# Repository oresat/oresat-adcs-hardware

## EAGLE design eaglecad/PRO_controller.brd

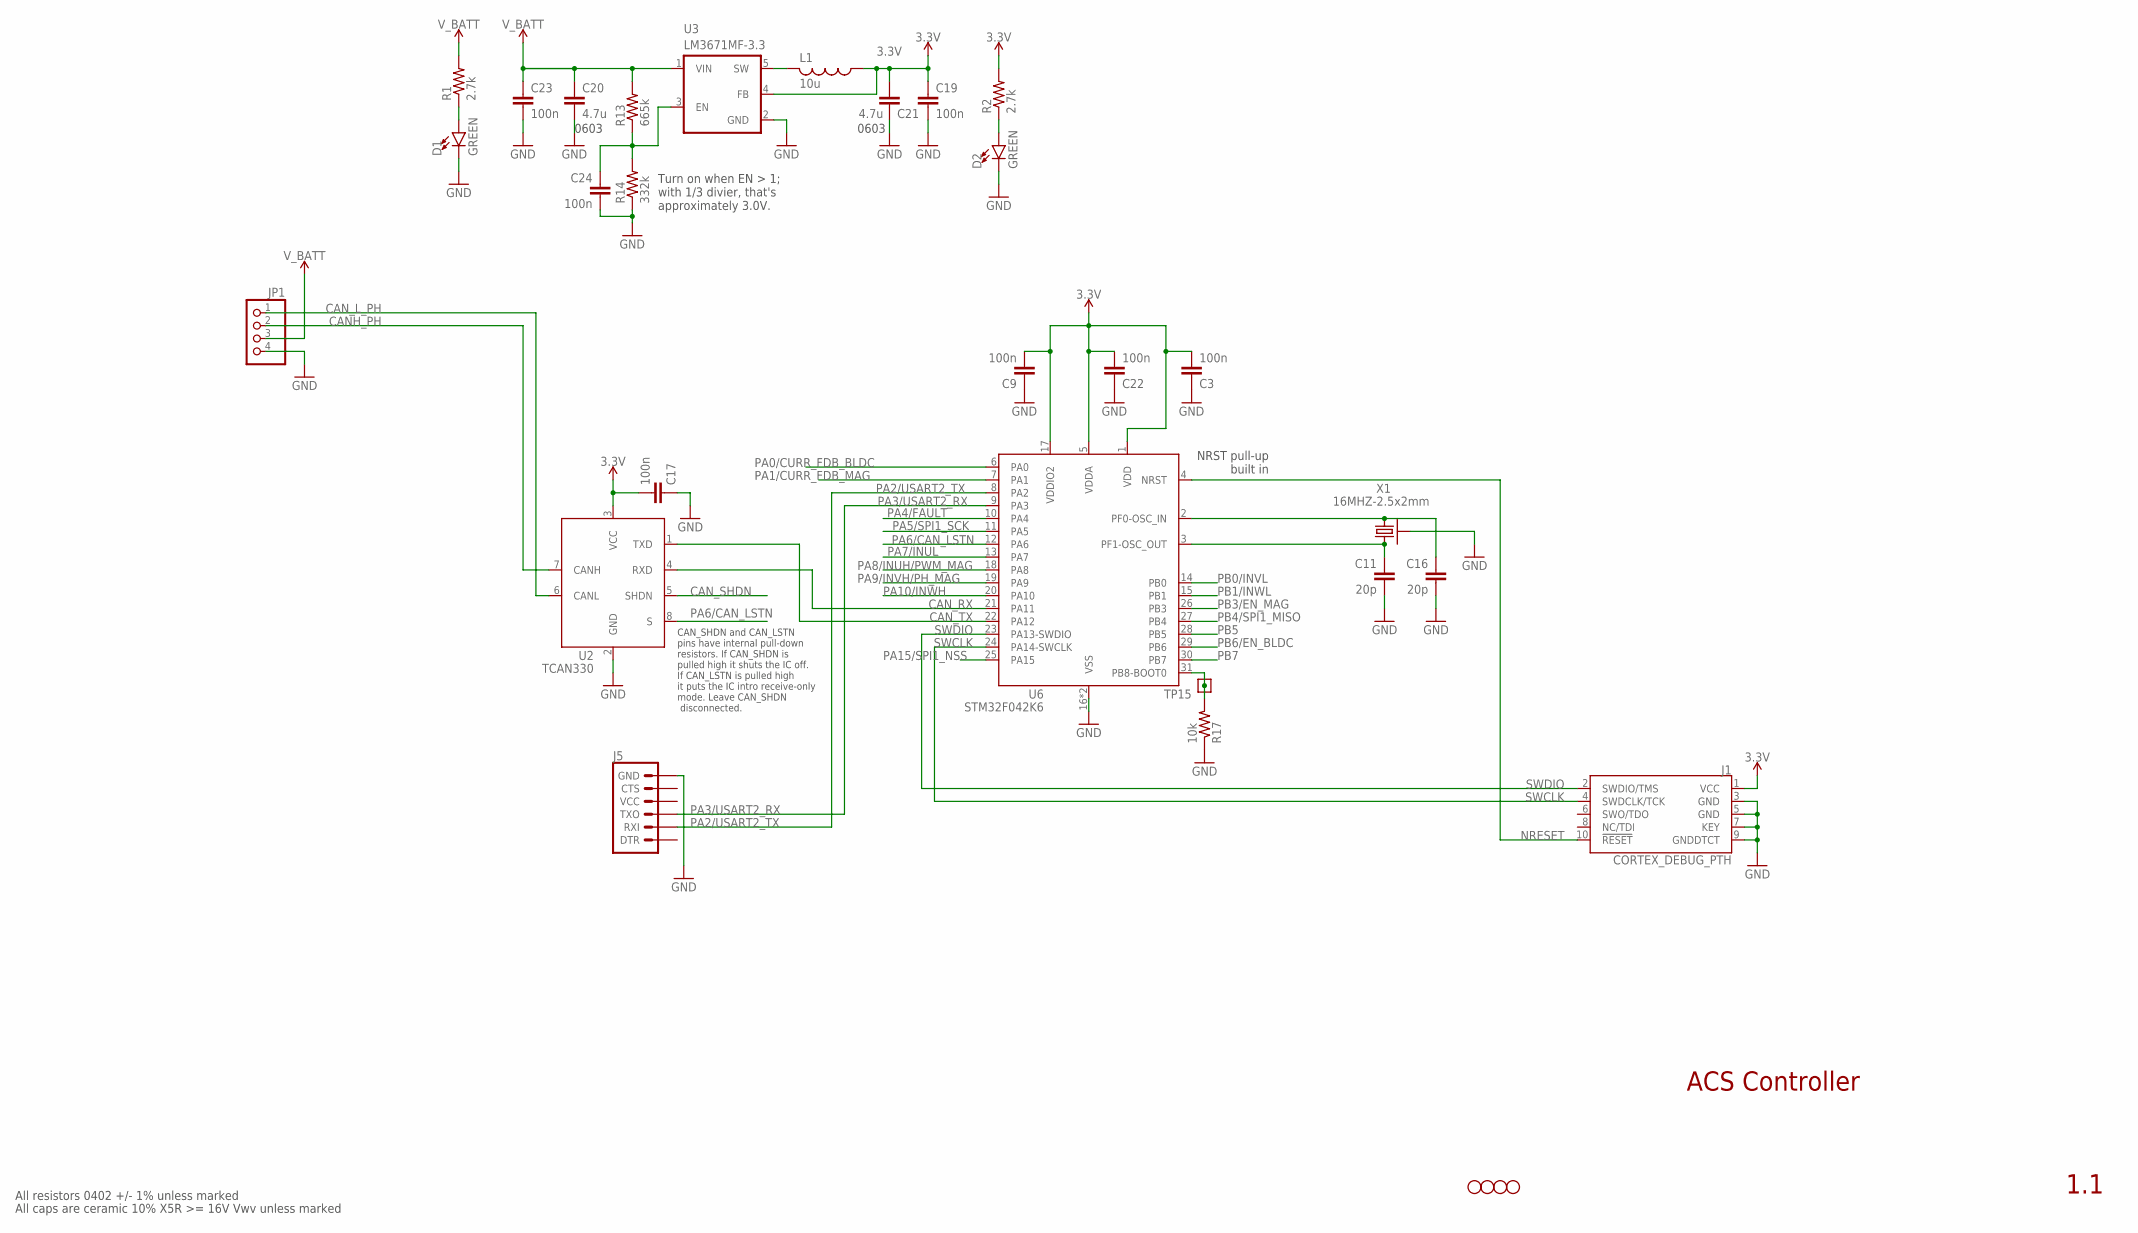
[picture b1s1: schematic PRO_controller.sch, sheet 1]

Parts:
C3, C9, C17, C19, C22, C23, C24: 100n; .0402-B-NOSILK; MPN CL05B104KO5NNNC
C11, C16: 20p; .0402-B-NOSILK; MPN CL05C200JB51PNC
C20, C21: 4.7u; C0603; MPN CL05B104KO5NNNC
D1, D2: GREEN; LED-0603
H1, H2, H3, H4: STAND-OFFTIGHT; STAND-OFF-TIGHT
J1: CORTEX_DEBUG_PTH; 2X5-PTH-1.27MM
J5: 6_PIN_SERIAL_TARGETSILK; 6_PIN_SERIAL_TARGET_SIDE_W_SILK
JP1: PINHD-1X4; 1X04
L1: 10u; L2012C; MPN CB2012T100KR
R1, R2: 2.7k; .0402-B-NOSILK; MPN RC1005F6653CS
R13: 665k; .0402-B-NOSILK; MPN RC1005F6653CS
R14: 332k; .0402-B-NOSILK; MPN RC1005F3323CS
R17: 10k; .0402-B-NOSILK; MPN RC1005F6653CS
TP15: TEST-POINT; 2MM-TEST-POINT
U2: TCAN330; SOT23-8_TI-DCN; MPN TCAN330GDCNT
U3: LM3671MF-3.3; SOT23-5; MPN LM3671MF-3.3/NOPB
U6: STM32F042K6; QFP32-7X7; MPN STM32F042K6T7
X1: 16MHZ-2.5x2mm; CRYSTAL_2.5X2; MPN ECS-160-10-36Q-ES-TR

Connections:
3.3V: C3.2, C9.2, C17.2, C19.1, C21.1, C22.2, J1.1 (VCC), L1.1, R2.2, U2.3 (VCC), U3.4 (FB), U6.1 (VDD), U6.5 (VDDA), U6.17 (VDDIO2); also elsewhere on the board
BOOT: R17.2, TP15.1, U6.31 (PB8-BOOT0)
CANH_PH: JP1.2, U2.7 (CANH)
CAN_L_PH: JP1.1, U2.6 (CANL)
CAN_RX: U2.4 (RXD), U6.21 (PA11)
CAN_SHDN: U2.5 (SHDN)
CAN_TX: U2.1 (TXD), U6.22 (PA12)
CRYSTALIN: C16.1, U6.2 (PF0-OSC_IN), X1.1
CRYSTALOUT: C11.1, U6.3 (PF1-OSC_OUT), X1.3 (2)
GND: C3.1, C9.1, C11.2, C16.2, C17.1, C19.2, C20.2, C21.2, C22.1, C23.2, C24.2, D1.C, D2.C, J1.3 (GND), J1.5 (GND), J1.7 (KEY), J1.9 (GNDDTCT), J5.P$6 (GND), JP1.4, R14.1, R17.1, U2.2 (GND), U3.2 (GND), U6.16 (VSS), U6.32 (VSS), X1.2 (SHIELD), X1.4 (SHIELD); also elsewhere on the board
unnamed: D1.A, R1.1
unnamed: D2.A, R2.1
NRESET: J1.10 (!RESET), U6.4 (NRST)
PA0/CURR_FDB_BLDC: U6.6 (PA0); also elsewhere on the board
PA1/CURR_FDB_MAG: U6.7 (PA1); also elsewhere on the board
PA2/USART2_TX: J5.P$3 (RXI), U6.8 (PA2)
PA3/USART2_RX: J5.P$2 (TXO), U6.9 (PA3)
PA4/FAULT: U6.10 (PA4); also elsewhere on the board
PA5/SPI1_SCK: U6.11 (PA5); also elsewhere on the board
PA6/CAN_LSTN: U2.8 (S), U6.12 (PA6)
PA7/INUL: U6.13 (PA7); also elsewhere on the board
PA8/INUH/PWM_MAG: U6.18 (PA8); also elsewhere on the board
PA9/INVH/PH_MAG: U6.19 (PA9); also elsewhere on the board
PA10/INWH: U6.20 (PA10); also elsewhere on the board
PA15/SPI1_NSS: U6.25 (PA15); also elsewhere on the board
PB0/INVL: U6.14 (PB0); also elsewhere on the board
PB1/INWL: U6.15 (PB1); also elsewhere on the board
PB3/EN_MAG: U6.26 (PB3); also elsewhere on the board
PB4/SPI1_MISO: U6.27 (PB4); also elsewhere on the board
PB5: U6.28 (PB5)
PB6/EN_BLDC: U6.29 (PB6); also elsewhere on the board
PB7: U6.30 (PB7)
STEPD: L1.2, U3.5 (SW)
SWCLK: J1.4 (SWDCLK/TCK), U6.24 (PA14-SWCLK)
SWDIO: J1.2 (SWDIO/TMS), U6.23 (PA13-SWDIO)
VDIV: C24.1, R13.1, R14.2, U3.3 (EN)
V_BATT: C20.1, C23.1, JP1.3, R1.2, R13.2, U3.1 (VIN); also elsewhere on the board

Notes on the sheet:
NRST pull-up built in
Turn on when EN > 1; with 1/3 divier, that's approximately 3.0V.
ACS Controller
1.1
All resistors 0402 +/- 1% unless marked
All caps are ceramic 10% X5R >= 16V Vwv unless marked
0603
CAN_SHDN and CAN_LSTN pins have internal pull-down resistors. If CAN_SHDN is pulled high it shuts the IC off. If CAN_LSTN is pulled high it puts the IC intro receive-only mode. Leave CAN_SHDN disconnected.

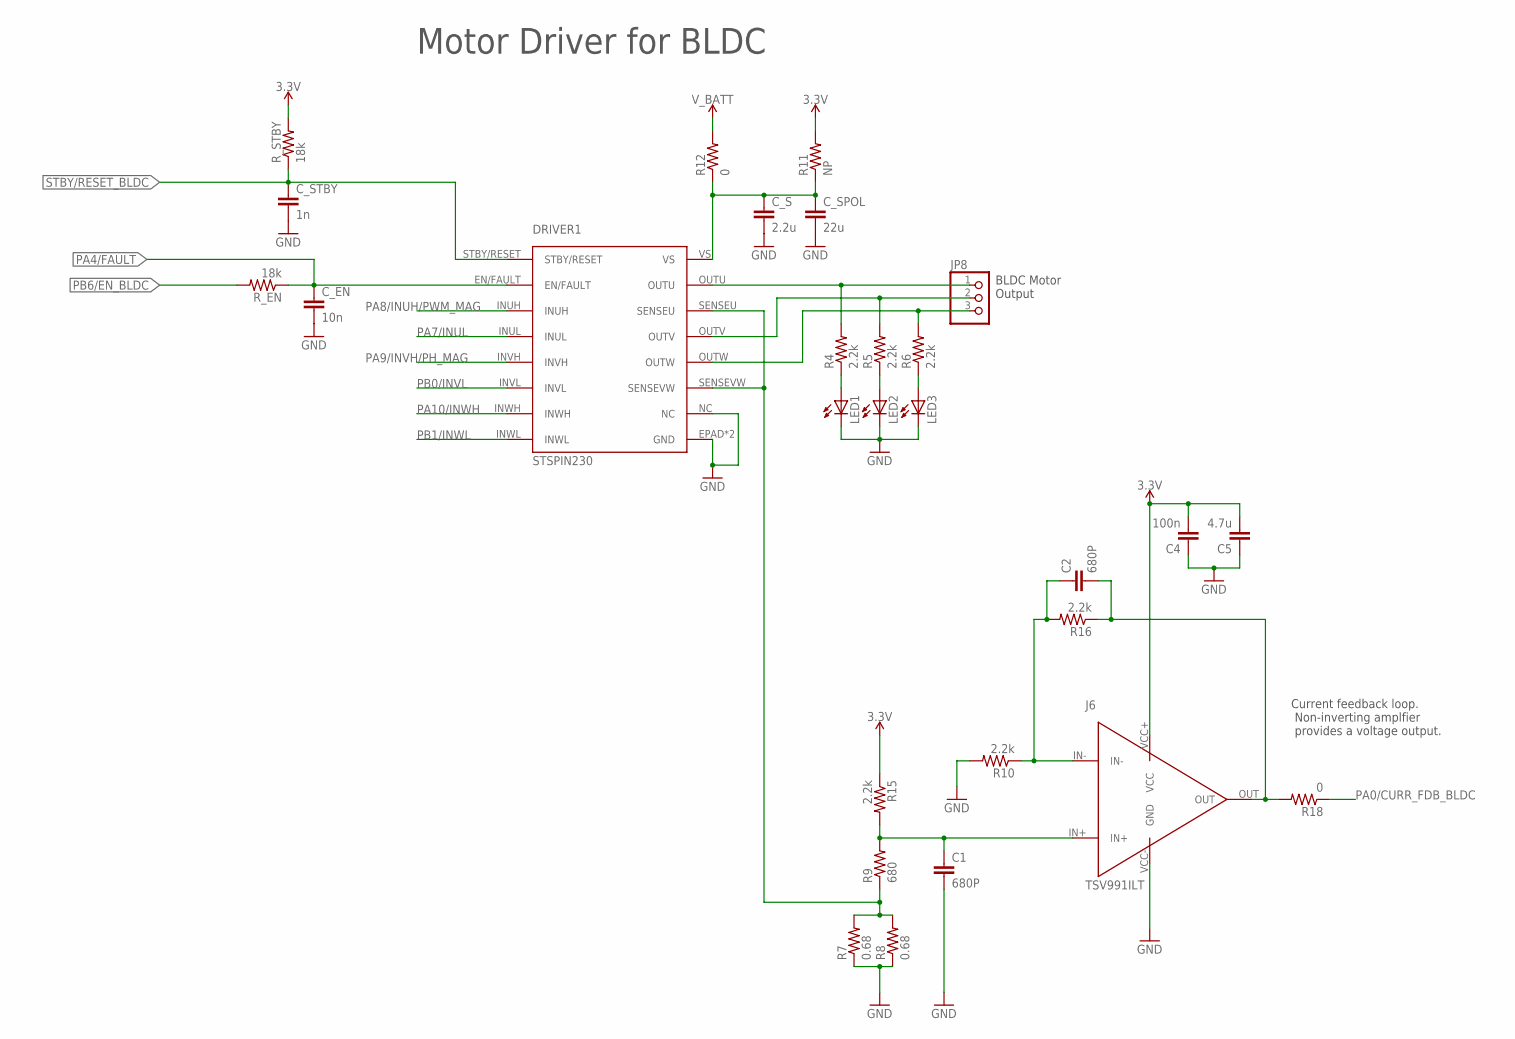
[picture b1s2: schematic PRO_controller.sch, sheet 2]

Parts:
C1, C2: 680P; C0402
C4: 100n; C0402
C5: 4.7u; C0402
C_EN: 10n; C0402
C_S: 2.2u; C0402
C_SPOL: 22u; C0402
C_STBY: 1n; C0402
DRIVER1: STSPIN230
J6: TSV991ILT; SOT23-5
JP8: PINHD-1X3; 1X03
LED1, LED2, LED3: LEDCHIP-LED0603; CHIP-LED0603
R4, R5, R6, R10, R15, R16: 2.2k; R0402
R7, R8: 0.68; R0402
R9: 680; R0402
R11: NP; R0402
R12, R18: 0; R0402
R_EN: 18k; R0402
R_STBY: 18k; R0402

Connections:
3.3V: C4.2, C5.2, J6.VCC+ (VCC), R11.2, R15.1, R_STBY.2; also elsewhere on the board
GND: C1.2, C4.1, C5.1, C_EN.2, C_S.2, C_SPOL.2, C_STBY.2, DRIVER1.EPAD (GND), DRIVER1.GND, DRIVER1.NC, J6.VCC- (GND), LED1.C, LED2.C, LED3.C, R7.1, R8.1, R10.2; also elsewhere on the board
unnamed: LED1.A, R4.1
unnamed: DRIVER1.OUTU, JP8.1, R4.2
unnamed: DRIVER1.OUTV, JP8.2, R5.2
unnamed: LED2.A, R5.1
unnamed: LED3.A, R6.1
unnamed: C_S.1, C_SPOL.1, DRIVER1.VS, R11.1, R12.1
unnamed: DRIVER1.SENSEU, DRIVER1.SENSEVW, R7.2, R8.2, R9.1
unnamed: C2.1, J6.IN-, R10.1, R16.2
unnamed: C1.1, J6.IN+, R9.2, R15.2
unnamed: DRIVER1.OUTW, JP8.3, R6.2
unnamed: C2.2, J6.OUT, R16.1, R18.2
PA0/CURR_FDB_BLDC: R18.1; also elsewhere on the board
PA4/FAULT: C_EN.1, DRIVER1.EN/FAULT, R_EN.1; also elsewhere on the board
PA7/INUL: DRIVER1.INUL; also elsewhere on the board
PA8/INUH/PWM_MAG: DRIVER1.INUH; also elsewhere on the board
PA9/INVH/PH_MAG: DRIVER1.INVH; also elsewhere on the board
PA10/INWH: DRIVER1.INWH; also elsewhere on the board
PB0/INVL: DRIVER1.INVL; also elsewhere on the board
PB1/INWL: DRIVER1.INWL; also elsewhere on the board
PB6/EN_BLDC: R_EN.2; also elsewhere on the board
STBY/RESET_BLDC: C_STBY.1, DRIVER1.STBY/RESET, R_STBY.1
V_BATT: R12.2; also elsewhere on the board

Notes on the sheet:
BLDC Motor Output
Current feedback loop. Non-inverting amplfier provides a voltage output.
Motor Driver for BLDC

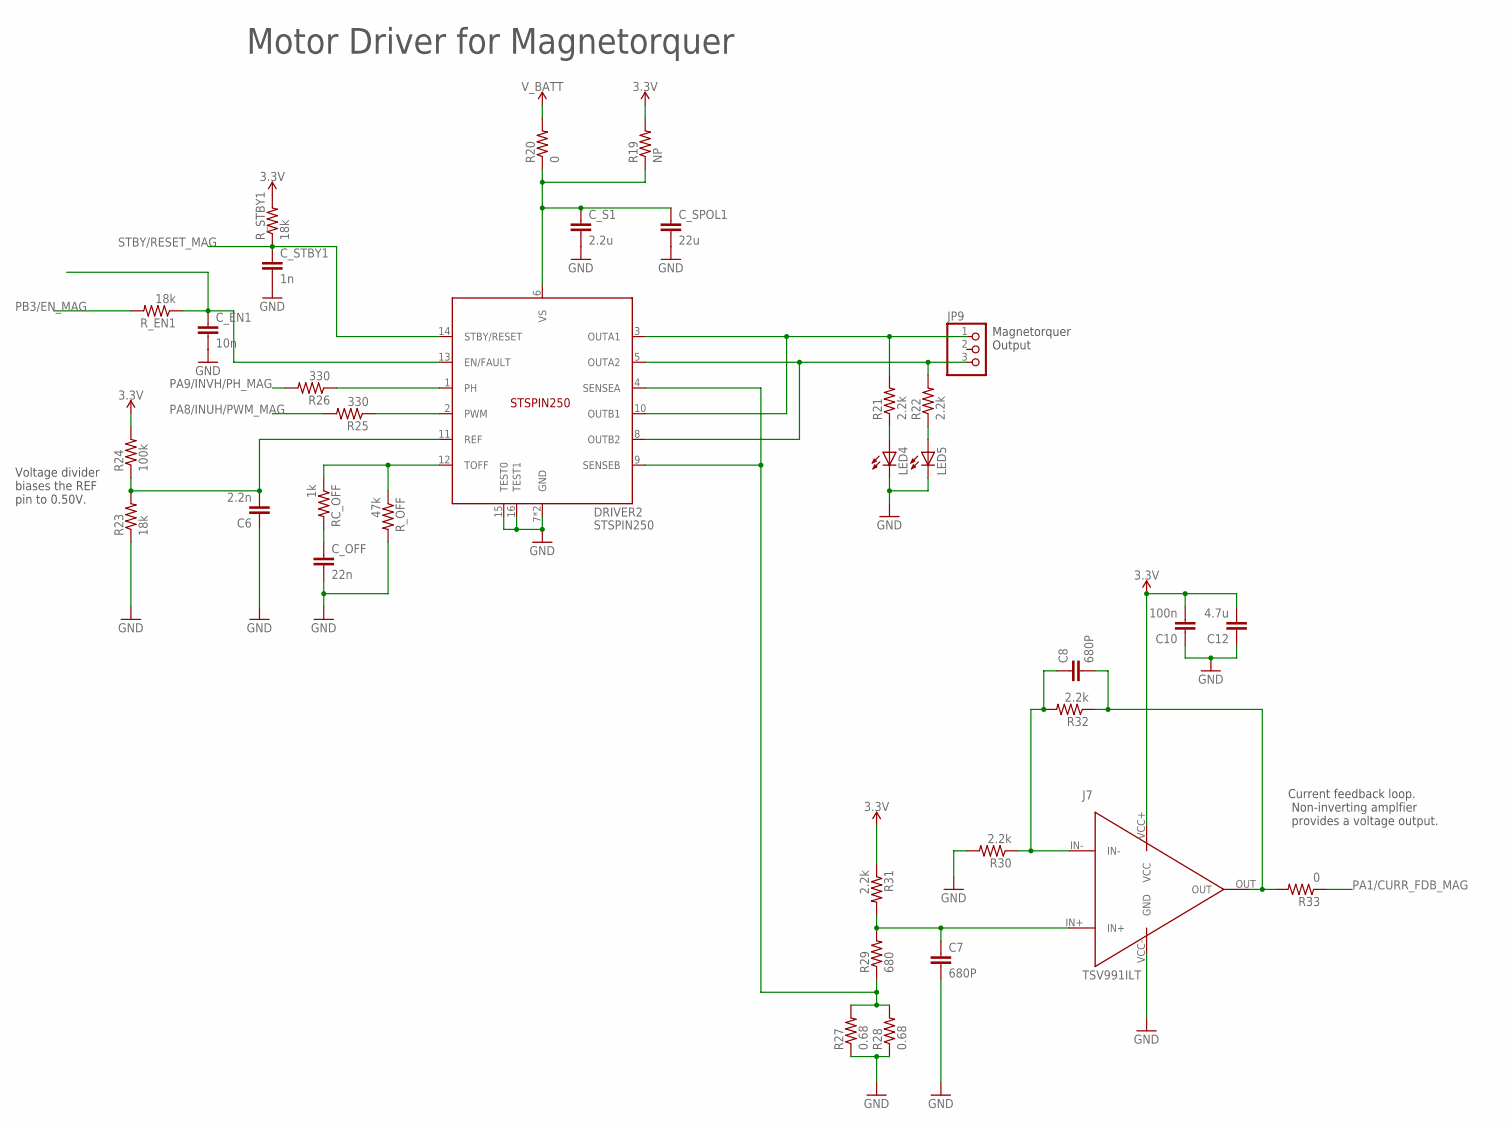
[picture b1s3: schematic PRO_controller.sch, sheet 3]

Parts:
C6: 2.2n; C0402
C7, C8: 680P; C0402
C10: 100n; C0402
C12: 4.7u; C0402
C_EN1: 10n; C0402
C_OFF: 22n; C0402
C_S1: 2.2u; C0402
C_SPOL1: 22u; C0402
C_STBY1: 1n; C0402
DRIVER2: STSPIN250; VFQFPN
J7: TSV991ILT; SOT23-5
JP9: PINHD-1X3; 1X03
LED4, LED5: LEDCHIP-LED0603; CHIP-LED0603
R19: NP; R0402
R20, R33: 0; R0402
R21, R22, R30, R31, R32: 2.2k; R0402
R23: 18k; R0402
R24: 100k; R0402
R25, R26: 330; R0402
R27, R28: 0.68; R0402
R29: 680; R0402
RC_OFF: 1k; R0402
R_EN1: 18k; R0402
R_OFF: 47k; R0402
R_STBY1: 18k; R0402

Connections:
3.3V: C10.2, C12.2, J7.VCC+ (VCC), R19.2, R24.2, R31.1, R_STBY1.2; also elsewhere on the board
FAULT_MAG: C_EN1.1, DRIVER2.13 (EN/FAULT), R_EN1.1
GND: C6.1, C7.2, C10.1, C12.1, C_EN1.2, C_OFF.2, C_S1.2, C_SPOL1.2, C_STBY1.2, DRIVER2.7 (GND), DRIVER2.15 (TEST0), DRIVER2.16 (TEST1), DRIVER2.EPAD (GND), J7.VCC- (GND), LED4.C, LED5.C, R23.1, R27.1, R28.1, R30.2, R_OFF.2; also elsewhere on the board
unnamed: DRIVER2.2 (PWM), R25.1
unnamed: DRIVER2.4 (SENSEA), DRIVER2.9 (SENSEB), R27.2, R28.2, R29.1
unnamed: DRIVER2.1 (PH), R26.1
unnamed: C7.1, J7.IN+, R29.2, R31.2
unnamed: C8.1, J7.IN-, R30.1, R32.2
unnamed: C_OFF.1, RC_OFF.2
unnamed: DRIVER2.12 (TOFF), RC_OFF.1, R_OFF.1
unnamed: C_S1.1, C_SPOL1.1, DRIVER2.6 (VS), R19.1, R20.1
unnamed: LED4.A, R21.1
unnamed: LED5.A, R22.1
unnamed: DRIVER2.3 (OUTA1), DRIVER2.10 (OUTB1), JP9.1, R21.2
unnamed: C6.2, DRIVER2.11 (REF), R23.2, R24.1
unnamed: DRIVER2.5 (OUTA2), DRIVER2.8 (OUTB2), JP9.3, R22.2
unnamed: C8.2, J7.OUT, R32.1, R33.2
PA1/CURR_FDB_MAG: R33.1; also elsewhere on the board
PA8/INUH/PWM_MAG: R25.2; also elsewhere on the board
PA9/INVH/PH_MAG: R26.2; also elsewhere on the board
PB3/EN_MAG: R_EN1.2; also elsewhere on the board
STBY/RESET_MAG: C_STBY1.1, DRIVER2.14 (STBY/RESET), R_STBY1.1
V_BATT: R20.2; also elsewhere on the board

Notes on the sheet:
Magnetorquer Output
Motor Driver for Magnetorquer
Current feedback loop. Non-inverting amplfier provides a voltage output.
Voltage divider biases the REF pin to 0.50V.

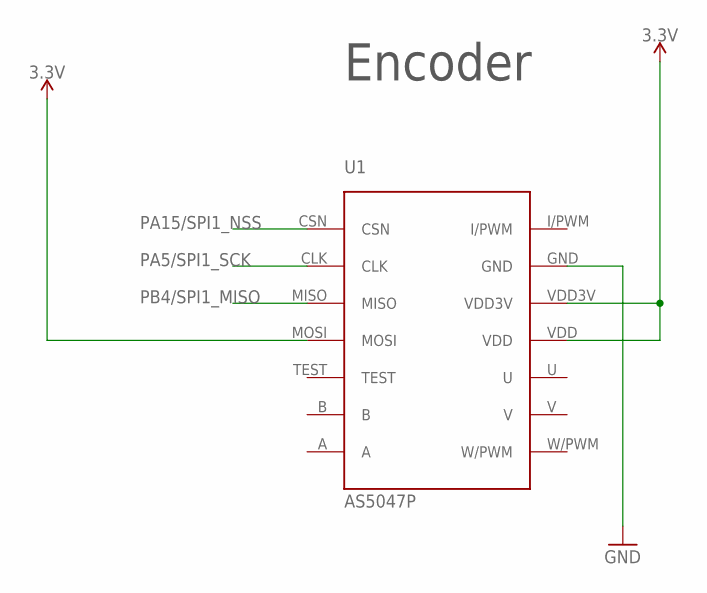
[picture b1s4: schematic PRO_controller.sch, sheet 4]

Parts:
U1: AS5047P; TSSOP14

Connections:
3.3V: U1.MOSI, U1.VDD, U1.VDD3V; also elsewhere on the board
GND: U1.GND; also elsewhere on the board
PA5/SPI1_SCK: U1.CLK; also elsewhere on the board
PA15/SPI1_NSS: U1.CSN; also elsewhere on the board
PB4/SPI1_MISO: U1.MISO; also elsewhere on the board

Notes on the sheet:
Encoder

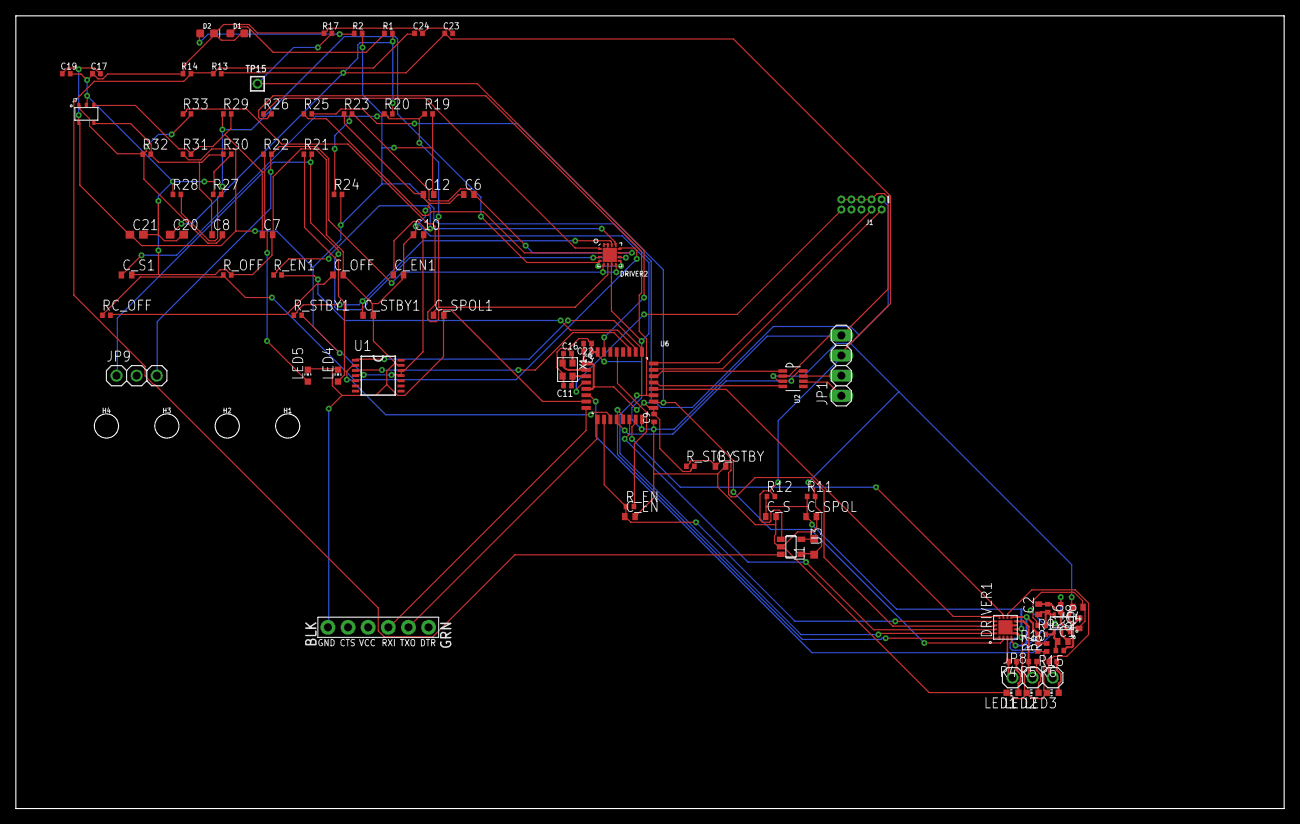
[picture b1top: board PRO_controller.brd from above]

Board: 2 copper layers, 160.0 x 100.0 mm, 94 parts (0 on the bottom side), 62 nets.

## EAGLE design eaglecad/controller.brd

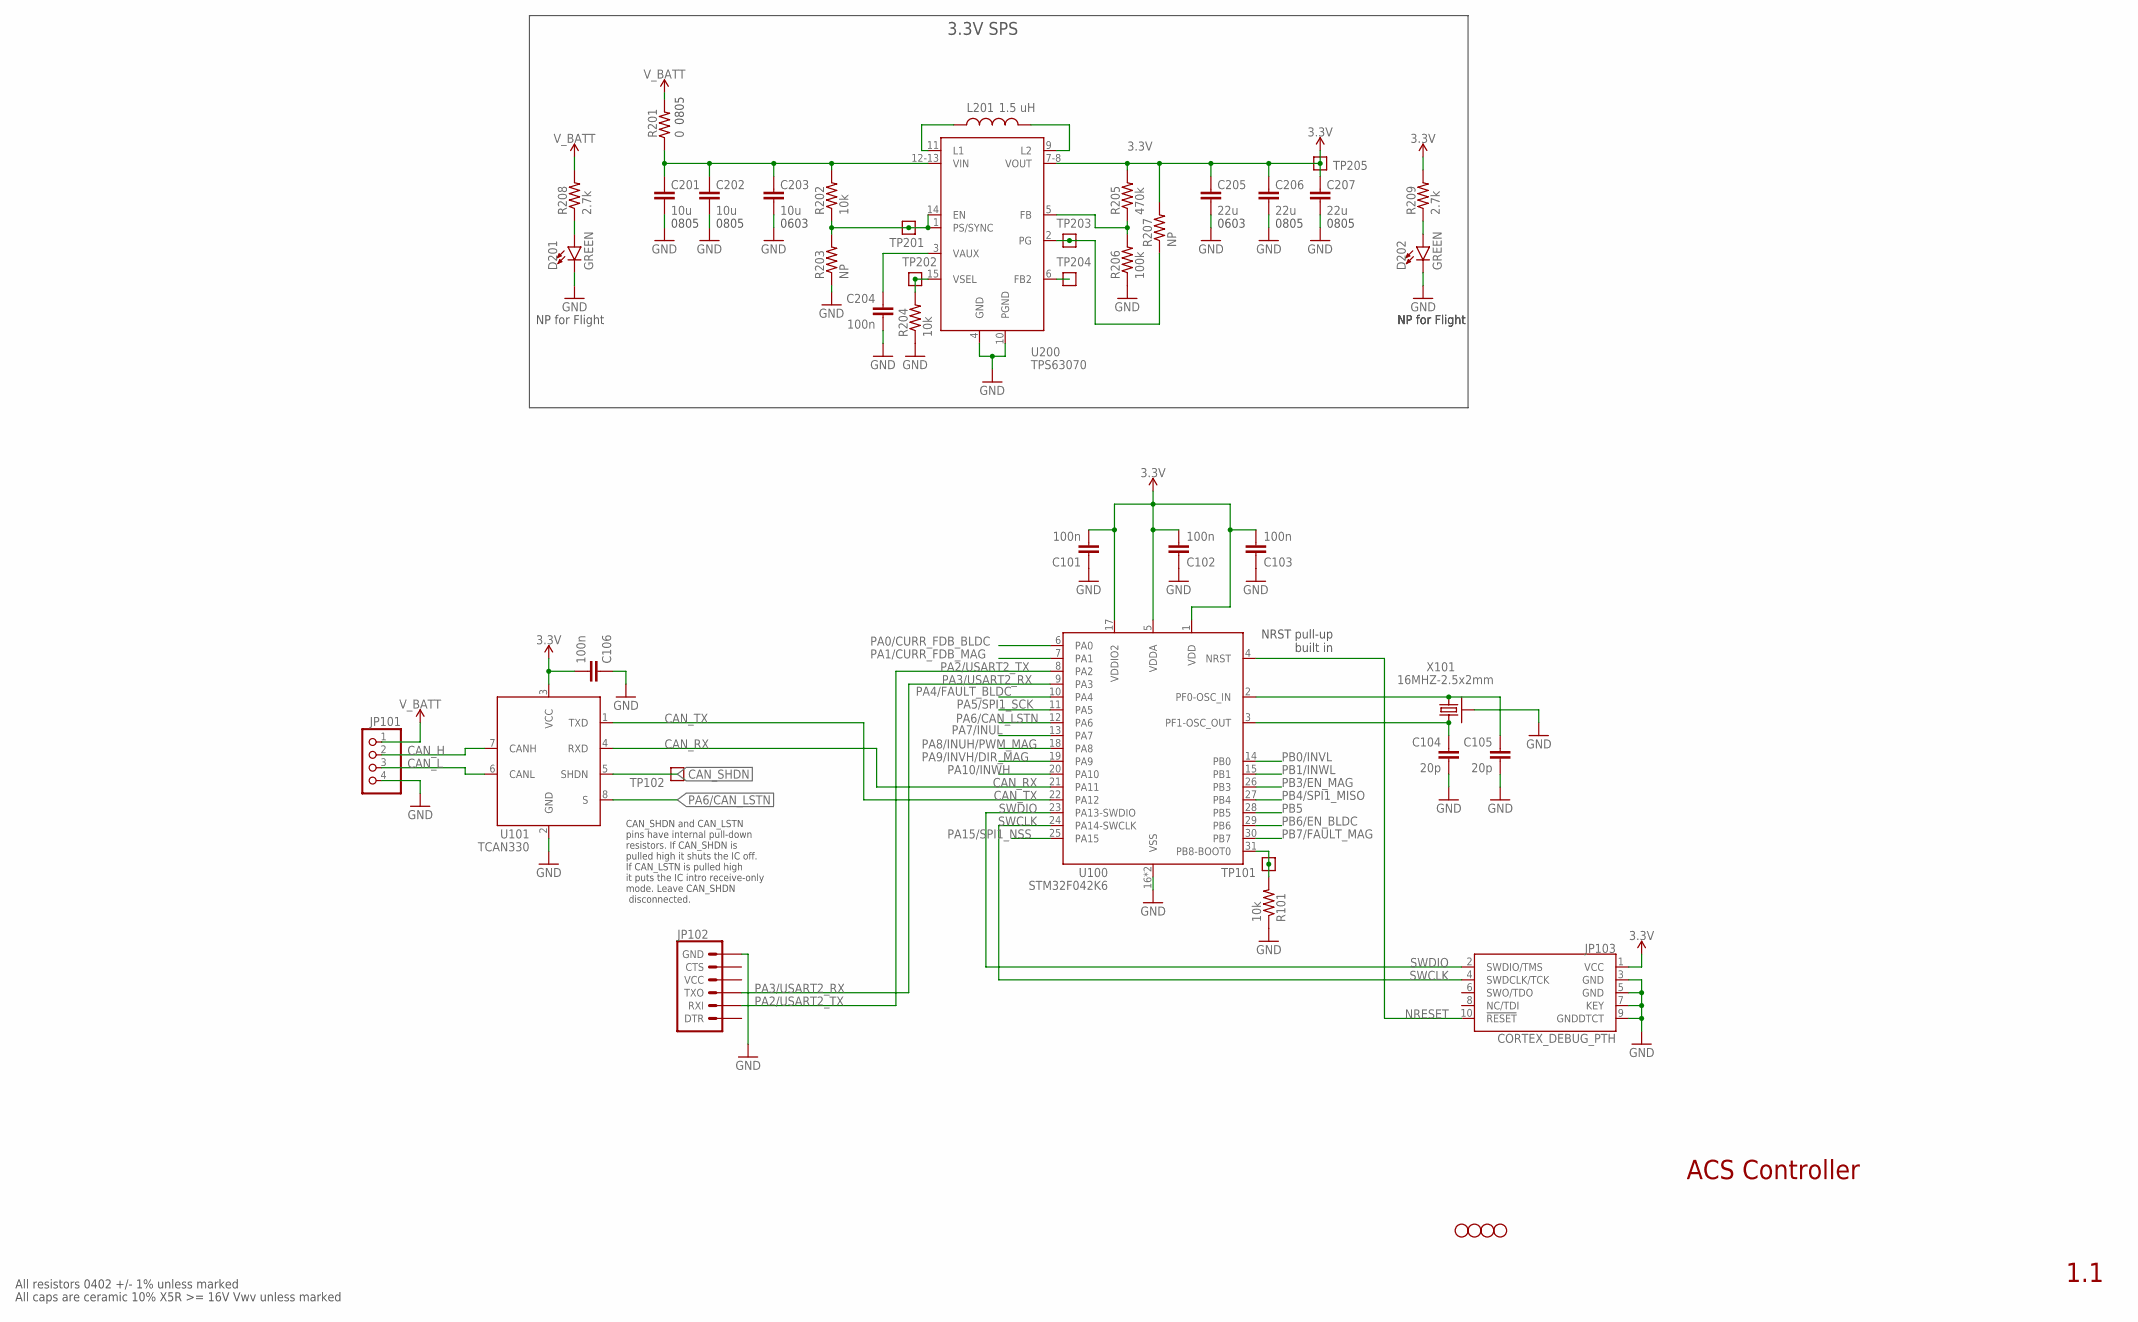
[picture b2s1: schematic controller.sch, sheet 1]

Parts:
C101, C102, C103, C106, C204: 100n; .0402-B-NOSILK; MPN CL05B104KO5NNNC
C104, C105: 20p; .0402-B-NOSILK; MPN CL05C200JB51PNC
C201, C202: 10u; .0805-B-NOSILK
C203: 10u; .0603-B-NOSILK; MPN CL05B104KO5NNNC
C205: 22u; .0603-B-NOSILK; MPN CL05B104KO5NNNC
C206, C207: 22u; .0805-B-NOSILK
D201, D202: GREEN; LED-0603
H1, H2, H3, H4: STAND-OFFTIGHT; STAND-OFF-TIGHT
JP101: PINHD-1X4; 1X04
JP102: 6_PIN_SERIAL_TARGETSILK; 6_PIN_SERIAL_TARGET_SIDE_W_SILK
JP103: CORTEX_DEBUG_PTH; 2X5-PTH-1.27MM
L201: 1.5 uH; L-COILCRAFT-XFL4020; MPN XFL4020-152ME
R101, R202, R204: 10k; .0402-B-NOSILK; MPN RC1005F6653CS
R201: 0; .0805-B-NOSILK; MPN MCR10EZPJ000
R203, R207: NP; .0402-B-NOSILK; MPN RC1005F6653CS
R205: 470k; .0402-B-NOSILK; MPN RC1005F6653CS
R206: 100k; .0402-B-NOSILK; MPN RC1005F6653CS
R208, R209: 2.7k; .0402-B-NOSILK; MPN RC1005F6653CS
TP101, TP102, TP201, TP202, TP203, TP204, TP205: TEST-POINT; 2MM-TEST-POINT
U100: STM32F042K6; QFP32-7X7; MPN STM32F042K6T7
U101: TCAN330; SOT23-8_TI-DCN; MPN TCAN330GDCNT
U200: TPS63070; TPS63070X
X101: 16MHZ-2.5x2mm; CRYSTAL_2.5X2; MPN ECS-160-10-36Q-ES-TR

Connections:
3.3V: C101.2, C102.2, C103.2, C106.2, C205.1, C206.1, C207.1, JP103.1 (VCC), R205.2, R207.2, R209.2, TP205.1, U100.1 (VDD), U100.5 (VDDA), U100.17 (VDDIO2), U101.3 (VCC), U200.7-8 (VOUT); also elsewhere on the board
BOOT: R101.2, TP101.1, U100.31 (PB8-BOOT0)
CAN_H: JP101.2, U101.7 (CANH)
CAN_L: JP101.3, U101.6 (CANL)
CAN_RX: U100.21 (PA11), U101.4 (RXD)
CAN_SHDN: TP102.1, U101.5 (SHDN)
CAN_TX: U100.22 (PA12), U101.1 (TXD)
CRYSTALIN: C105.1, U100.2 (PF0-OSC_IN), X101.1
CRYSTALOUT: C104.1, U100.3 (PF1-OSC_OUT), X101.3 (2)
GND: C101.1, C102.1, C103.1, C104.2, C105.2, C106.1, C201.2, C202.2, C203.2, C204.2, C205.2, C206.2, C207.2, D201.C, D202.C, JP101.4, JP102.P$6 (GND), JP103.3 (GND), JP103.5 (GND), JP103.7 (KEY), JP103.9 (GNDDTCT), R101.1, R203.1, R204.1, R206.1, U100.16 (VSS), U100.32 (VSS), U101.2 (GND), U200.4 (GND), U200.10 (PGND), X101.2 (SHIELD), X101.4 (SHIELD); also elsewhere on the board
unnamed: D201.A, R208.1
unnamed: D202.A, R209.1
NRESET: JP103.10 (!RESET), U100.4 (NRST); also elsewhere on the board
PA0/CURR_FDB_BLDC: U100.6 (PA0); also elsewhere on the board
PA1/CURR_FDB_MAG: U100.7 (PA1); also elsewhere on the board
PA4/FAULT_BLDC: U100.10 (PA4); also elsewhere on the board
PA5/SPI1_SCK: U100.11 (PA5); also elsewhere on the board
PA6/CAN_LSTN: U100.12 (PA6), U101.8 (S)
PA7/INUL: U100.13 (PA7); also elsewhere on the board
PA8/INUH/PWM_MAG: U100.18 (PA8); also elsewhere on the board
PA9/INVH/DIR_MAG: U100.19 (PA9); also elsewhere on the board
PA10/INWH: U100.20 (PA10); also elsewhere on the board
PA15/SPI1_NSS: U100.25 (PA15); also elsewhere on the board
PB0/INVL: U100.14 (PB0); also elsewhere on the board
PB1/INWL: U100.15 (PB1); also elsewhere on the board
PB3/EN_MAG: U100.26 (PB3); also elsewhere on the board
PB4/SPI1_MISO: U100.27 (PB4); also elsewhere on the board
PB5: U100.28 (PB5)
PB6/EN_BLDC: U100.29 (PB6); also elsewhere on the board
PB7/FAULT_MAG: U100.30 (PB7); also elsewhere on the board
SWCLK: JP103.4 (SWDCLK/TCK), U100.24 (PA14-SWCLK); also elsewhere on the board
SWDIO: JP103.2 (SWDIO/TMS), U100.23 (PA13-SWDIO); also elsewhere on the board
TPS-EN: R202.1, R203.2, TP201.1, U200.1 (PS/SYNC), U200.14 (EN)
TPS-FB: R205.1, R206.2, U200.5 (FB)
TPS-FB2: TP204.1, U200.6 (FB2)
TPS-L1: L201.1, U200.11 (L1)
TPS-L2: L201.2, U200.9 (L2)
TPS-PG: R207.1, TP203.1, U200.2 (PG)
TPS-VAUX: C204.1, U200.3 (VAUX)
TPS-VIN: C201.1, C202.1, C203.1, R201.1, R202.2, U200.12-13 (VIN)
TPS-VSEL: R204.2, TP202.1, U200.15 (VSEL)
V_BATT: JP101.1, R201.2, R208.2; also elsewhere on the board

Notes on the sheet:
NRST pull-up built in
ACS Controller
1.1
All resistors 0402 +/- 1% unless marked
All caps are ceramic 10% X5R >= 16V Vwv unless marked
CAN_SHDN and CAN_LSTN pins have internal pull-down resistors. If CAN_SHDN is pulled high it shuts the IC off. If CAN_LSTN is pulled high it puts the IC intro receive-only mode. Leave CAN_SHDN disconnected.
0603
0805
3.3V SPS
NP for Flight

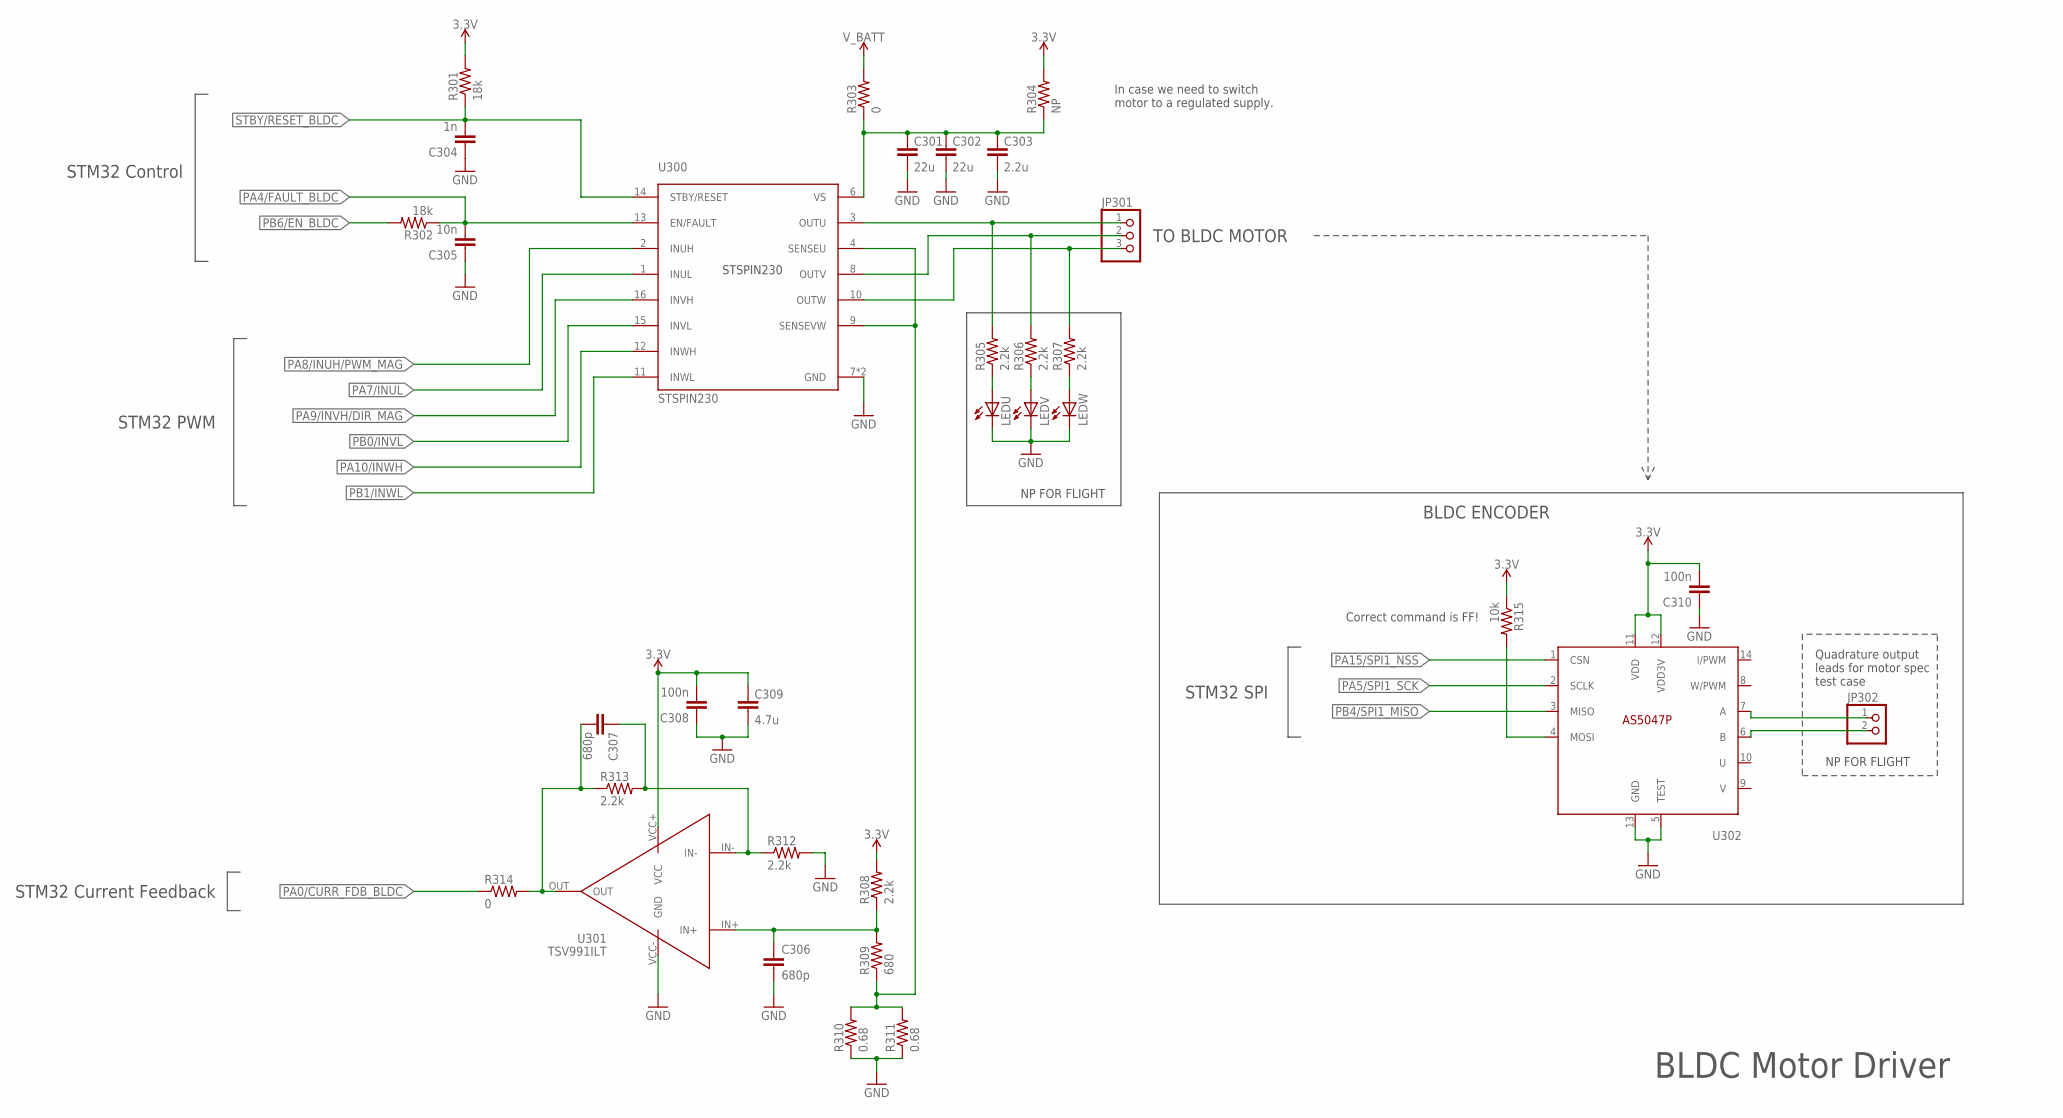
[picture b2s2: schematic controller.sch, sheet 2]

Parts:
C301, C302: 22u; .0603-B-NOSILK; MPN CL05B104KO5NNNC
C303: 2.2u; .0603-B-NOSILK; MPN CL05B104KO5NNNC
C304: 1n; .0402-B-NOSILK; MPN CL05B104KO5NNNC
C305: 10n; .0402-B-NOSILK; MPN CL05B104KO5NNNC
C306, C307: 680p; .0402-B-NOSILK; MPN CL05B104KO5NNNC
C308, C310: 100n; .0402-B-NOSILK; MPN CL05B104KO5NNNC
C309: 4.7u; .0603-B-NOSILK; MPN CL05B104KO5NNNC
JP301: PINHD-1X3; 1X03
JP302: PINHD-1X2; 1X02
LEDU: LEDCHIP-LED0603; CHIP-LED0603
LEDV: LEDCHIP-LED0603; CHIP-LED0603
LEDW: LEDCHIP-LED0603; CHIP-LED0603
R301, R302: 18k; .0402-B-NOSILK; MPN RC1005F6653CS
R303: 0; .0805-B-NOSILK
R304: NP; .0805-B-NOSILK
R305, R306, R307: 2.2k; .0805-B-NOSILK
R308, R312, R313: 2.2k; .0402-B-NOSILK; MPN RC1005F6653CS
R309: 680; .0402-B-NOSILK; MPN RC1005F6653CS
R310, R311: 0.68; .0805-B-NOSILK
R314: 0; .0402-B-NOSILK; MPN RC1005F6653CS
R315: 10k; .0402-B-NOSILK; MPN RC1005F6653CS
U300: STSPIN230; VFQFPN
U301: TSV991ILT; SOT23-5
U302: AS5047P; TSSOP14

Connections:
3.3V: C308.2, C309.1, C310.2, R301.2, R304.2, R308.2, R315.1, U301.VCC+ (VCC), U302.11 (VDD), U302.12 (VDD3V); also elsewhere on the board
GND: C301.2, C302.2, C303.2, C304.1, C305.1, C306.2, C308.1, C309.2, C310.1, LEDU.C, LEDV.C, LEDW.C, R310.1, R311.1, R312.2, U300.7 (GND), U300.EPAD (GND), U301.VCC- (GND), U302.5 (TEST), U302.13 (GND); also elsewhere on the board
unnamed: R315.2, U302.4 (MOSI)
unnamed: JP302.1, U302.7 (A)
unnamed: LEDU.A, R305.1
unnamed: LEDV.A, R306.1
unnamed: LEDW.A, R307.1
unnamed: C301.1, C302.1, C303.1, R303.1, R304.1, U300.6 (VS)
unnamed: JP302.2, U302.6 (B)
unnamed: C307.1, R312.1, R313.2, U301.IN-
unnamed: C306.1, R308.1, R309.2, U301.IN+
unnamed: C307.2, R313.1, R314.2, U301.OUT
PA0/CURR_FDB_BLDC: R314.1; also elsewhere on the board
PA4/FAULT_BLDC: C305.2, R302.1, U300.13 (EN/FAULT); also elsewhere on the board
PA5/SPI1_SCK: U302.2 (SCLK); also elsewhere on the board
PA7/INUL: U300.1 (INUL); also elsewhere on the board
PA8/INUH/PWM_MAG: U300.2 (INUH); also elsewhere on the board
PA9/INVH/DIR_MAG: U300.16 (INVH); also elsewhere on the board
PA10/INWH: U300.12 (INWH); also elsewhere on the board
PA15/SPI1_NSS: U302.1 (CSN); also elsewhere on the board
PB0/INVL: U300.15 (INVL); also elsewhere on the board
PB1/INWL: U300.11 (INWL); also elsewhere on the board
PB4/SPI1_MISO: U302.3 (MISO); also elsewhere on the board
PB6/EN_BLDC: R302.2; also elsewhere on the board
SENSE_BLDC: R309.1, R310.2, R311.2, U300.4 (SENSEU), U300.9 (SENSEVW)
STBY/RESET_BLDC: C304.2, R301.1, U300.14 (STBY/RESET)
U: JP301.1, R305.2, U300.3 (OUTU)
V: JP301.2, R306.2, U300.8 (OUTV)
V_BATT: R303.2; also elsewhere on the board
W: JP301.3, R307.2, U300.10 (OUTW)

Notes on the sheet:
TO BLDC MOTOR
STM32 Current Feedback
BLDC Motor Driver
NP FOR FLIGHT
STM32 PWM
STM32 Control
In case we need to switch motor to a regulated supply.
Correct command is FF!
STM32 SPI
BLDC ENCODER
Quadrature output leads for motor spec test case

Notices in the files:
parts and their libraries:
SparkFun-LED: Licensing: Creative Commons ShareAlike 4.0 International - https://creativecommons.org/licenses/by-sa/4.0
